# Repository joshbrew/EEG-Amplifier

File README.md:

## EEG Differential Amplifier

The main circuit here uses 4 low noise op amps to achieve EEG differential amplification. This should plug into any single ended ADC (or put your negative input to ground) to allow even as low as 10 bit EEG.

The amps cost 10 cents from TI, not including the PCB which will vary.

The reference design is for 1000x gain at 5v with a 2.5v voltage reference. All calculations are in the pdf for your needs.

### Resources
- [Differential Amp BOM](https://docs.google.com/spreadsheets/d/1rzFOKtwm5F1gYTblCt51H4664hxHK5iFGmpR6K0Omsg/edit?usp=sharing)
- [Gain Amp BOM](https://docs.google.com/spreadsheets/d/1fu1xdZPcOAWwaKk6sFUOHw02OROvW1wCZvjth2xU8xA/edit?usp=sharing)
- [Design reference](https://github.com/joshbrew/EEG-Amplifier/blob/main/EEG_Active_electrode_design.pdf) by Abishek Parikh. 
Other info pulled from datasheets.

Note my previous OPA202 config was incorrect. And use this formula for calculating the bandpass: 
<table>
  <tr>
    <td>
      <br/>
      In our config, + is our reference <br/> 
      (e.g. ear for EEG or opposite wrist for ECG)
    </td>
    <td>
      
    </td>
    <td>
      Gain = R2 / R1
    </td>
  </tr>
</table>

### OPA4202ID/TL084CDR/TL084OD (or compatible SOIC14) SMT mount.

OPA4202ID is more expensive but MUCH better quality, with better input impedance (3TΩ) and a 9nV/sqrt(Hz) noise density starting at 0.1Hz. The TL084's spectral noise doesn't bottom out until near 1kHz.

### 4mm Snap Button Electrode Mountholes

Sized for Florida Instruments reusable plastic snap electrodes.

### TL084HCN (A,B,H, etc) Thruhole amp (for DIY)

### OPA4202IPW or OPA4377 (or  compatible TSSOP14) SMT mount.

### Schematics

The BioAmp EXG Pill has a different layout you can check out. Same chipset.

### Noise vs Measured Bandwidth on OPA4202

Note: Noise calcs are probably inaccurate. Lower frequencies have higher noise density. Adjust bandpass accordingly.

TL084 noise density:

OPA4202 noise density:

OPA4202 or OPA4377 are about a dollar. I think the 4202 is better based on the noise.

## Also included in CAD/singular_amps

Single and Dual OPA202/OPA2202 gain amplifiers. E.g. for pre-amplification. Great low frequency noise density. 

### OPA202 (or pin compatible) VSSOP8 package (or pin compatible)

### OPA202 VSSOP8 package with 4mm electrode mount

### OPA202 SOIC8 package and thruhole resistors/capacitors (easier to hand solder)

### OPA202 SOIC8 package thruhole with 4mm electrode mount

EAGLE drawings by Josh Brewster. Works in free EAGLE or you can import them elsewhere usually.

Best prices are on TI.com just FYI...

Free source! Definitely question my circuitry before you use it.

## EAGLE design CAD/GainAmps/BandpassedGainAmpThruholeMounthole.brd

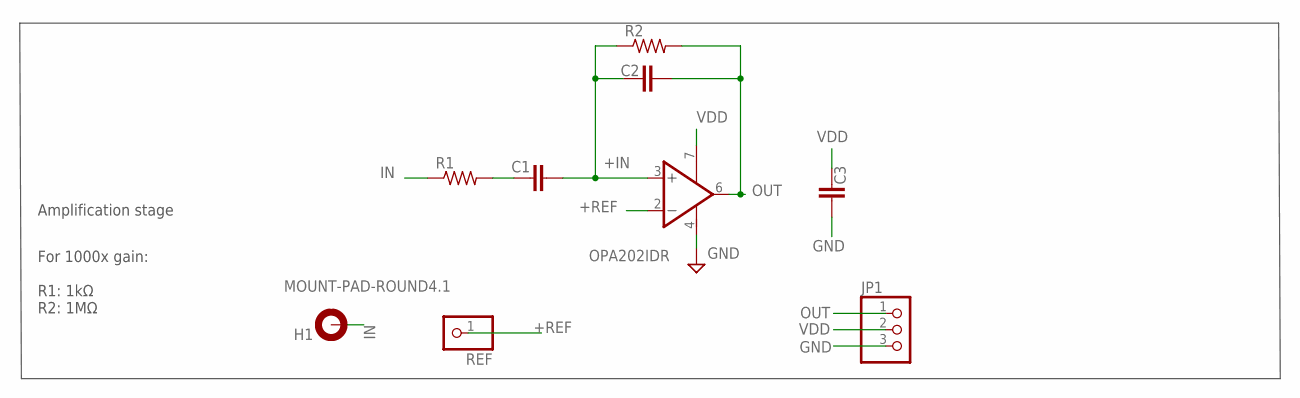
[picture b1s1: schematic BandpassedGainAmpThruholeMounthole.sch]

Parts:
C1, C2, C3: C2.5/2; C2.5-2
H1: MOUNT-PAD-ROUND4.1; 4,1-PAD
JP1: PINHD-1X3; 1X03
R1, R2: R-US_0204/5; 0204/5
REF: PINHD-1X1; 1X01
U1: OPA202IDR; SOIC127P600X175-8N

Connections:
+IN: C1.2, C2.1, R2.1, U1.3 (+IN)
+REF: REF.1, U1.2 (-IN)
GND: C3.2, JP1.3, U1.4 (V-)
IN: H1.B4,1, R1.1
OUT: C2.2, JP1.1, R2.2, U1.6 (OUT)
R1C1: C1.1, R1.2
VDD: C3.1, JP1.2, U1.7 (V+)

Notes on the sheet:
Amplification stage
For 1000x gain: R1: 1kΩ R2: 1MΩ

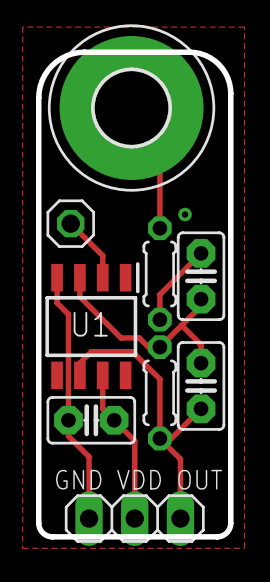
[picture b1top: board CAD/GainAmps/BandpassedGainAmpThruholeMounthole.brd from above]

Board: 2 copper layers, 10.7 x 26.9 mm, 9 parts (0 on the bottom side), 7 nets.

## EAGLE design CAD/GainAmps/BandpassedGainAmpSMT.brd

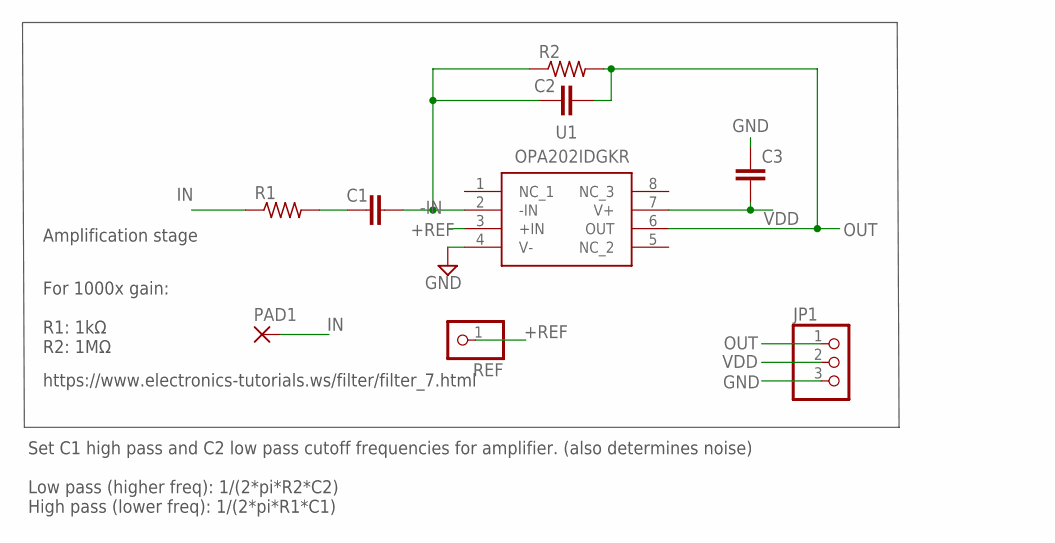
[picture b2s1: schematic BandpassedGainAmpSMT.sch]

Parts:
C1, C2, C3: C-EUC0402; C0402
JP1: PINHD-1X3; 1X03
PAD1: 3,17/1,1
R1, R2: R-US_R0402; R0402
REF: PINHD-1X1; 1X01
U1: OPA202IDGKR; SOP65P490X110-8N

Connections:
+REF: REF.1, U1.3 (+IN)
-IN: C1.2, C2.1, R2.1, U1.2 (-IN)
GND: C3.1, JP1.3, U1.4 (V-)
IN: PAD1.1, R1.1
OUT: C2.2, JP1.1, R2.2, U1.6 (OUT)
R1C1: C1.1, R1.2
VDD: C3.2, JP1.2, U1.7 (V+)

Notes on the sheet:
Amplification stage
For 1000x gain: R1: 1kΩ R2: 1MΩ
Set C1 high pass and C2 low pass cutoff frequencies for amplifier. (also determines noise) Low pass (higher freq): 1/(2*pi*R2*C2) High pass (lower freq): 1/(2*pi*R1*C1)
https://www.electronics-tutorials.ws/filter/filter_7.html

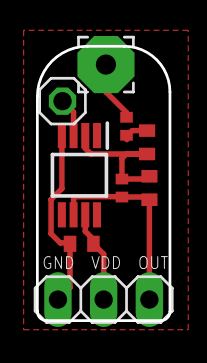
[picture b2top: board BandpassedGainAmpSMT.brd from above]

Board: 2 copper layers, 7.4 x 15.2 mm, 9 parts (0 on the bottom side), 7 nets.

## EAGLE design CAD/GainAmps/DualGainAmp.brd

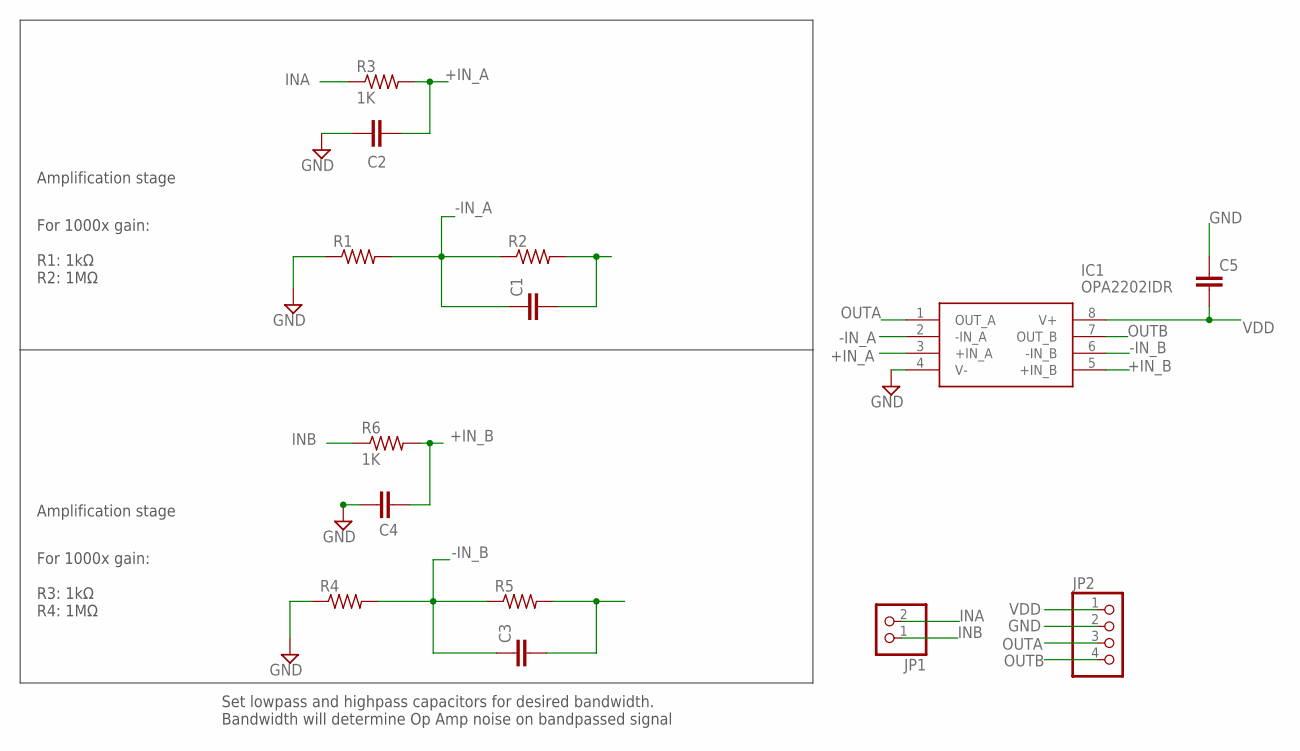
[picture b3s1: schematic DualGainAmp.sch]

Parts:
C1, C2, C3, C4: C-EUC0402; C0402
C5: C2.5/2; C2.5-2
IC1: OPA2202IDR; SOIC127P600X175-8N
JP1: PINHD-1X2; 1X02
JP2: PINHD-1X4; 1X04
R1, R2, R4, R5: R-US_0204/5; 0204/5
R3, R6: 1K; 0204/5

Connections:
+IN_A: C2.2, IC1.3 (+IN_A), R3.2
+IN_B: C4.2, IC1.5 (+IN_B), R6.2
-IN_A: C1.1, IC1.2 (-IN_A), R1.2, R2.1
-IN_B: C3.1, IC1.6 (-IN_B), R4.2, R5.1
GND: C2.1, C4.1, C5.1, IC1.4 (V-), JP2.2, R1.1, R4.1
INA: JP1.2, R3.1
INB: JP1.1, R6.1
unnamed: C1.2, R2.2
unnamed: C3.2, R5.2
OUTA: IC1.1 (OUT_A), JP2.3
OUTB: IC1.7 (OUT_B), JP2.4
VDD: C5.2, IC1.8 (V+), JP2.1

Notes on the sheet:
Amplification stage
For 1000x gain: R3: 1kΩ R4: 1MΩ
For 1000x gain: R1: 1kΩ R2: 1MΩ
Set lowpass and highpass capacitors for desired bandwidth. Bandwidth will determine Op Amp noise on bandpassed signal

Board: 2 copper layers, 14 parts (0 on the bottom side), 12 nets, no tracks yet.

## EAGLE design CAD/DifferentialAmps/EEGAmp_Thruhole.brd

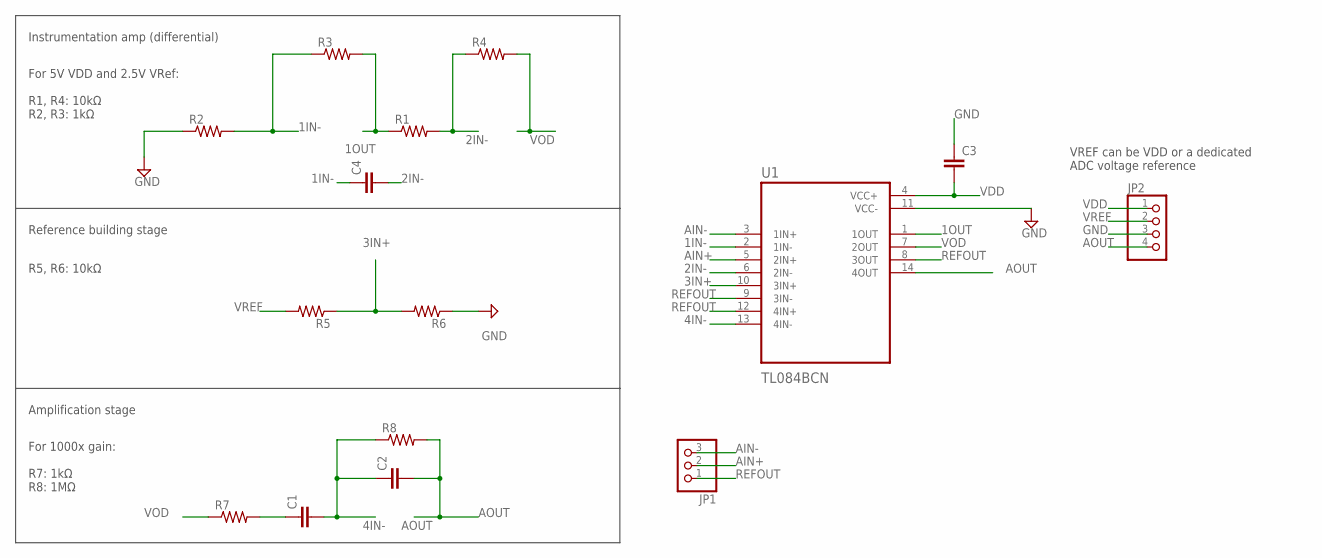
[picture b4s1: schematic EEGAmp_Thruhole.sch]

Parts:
C1, C2, C3, C4: C2.5/2; C2.5-2
JP1: PINHD-1X3; 1X03
JP2: PINHD-1X4; 1X04
R1, R2, R3, R4, R5, R6, R7, R8: R-US_0204/5; 0204/5
U1: TL084BCN; DIP794W45P254L1969H508Q14

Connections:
1IN-: C4.1, R2.2, R3.1, U1.2 (1IN-)
1OUT: R1.1, R3.2, U1.1 (1OUT)
2IN-: C4.2, R1.2, R4.1, U1.6 (2IN-)
3IN+: R5.1, R6.2, U1.10 (3IN+)
4IN-: C1.2, C2.1, R8.1, U1.13 (4IN-)
AIN+: JP1.2, U1.5 (2IN+)
AIN-: JP1.3, U1.3 (1IN+)
AOUT: C2.2, JP2.4, R8.2, U1.14 (4OUT)
GND: C3.1, JP2.3, R2.1, R6.1, U1.11 (VCC-)
unnamed: C1.1, R7.2
REFOUT: JP1.1, U1.8 (3OUT), U1.9 (3IN-), U1.12 (4IN+)
VDD: C3.2, JP2.1, U1.4 (VCC+)
VOD: R4.2, R7.1, U1.7 (2OUT)
VREF: JP2.2, R5.2

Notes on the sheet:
Instrumentation amp (differential)
Reference building stage
Amplification stage
For 5V VDD and 2.5V VRef: R1, R4: 10kΩ R2, R3: 1kΩ
R5, R6: 10kΩ
For 1000x gain: R7: 1kΩ R8: 1MΩ
VREF can be VDD or a dedicated ADC voltage reference

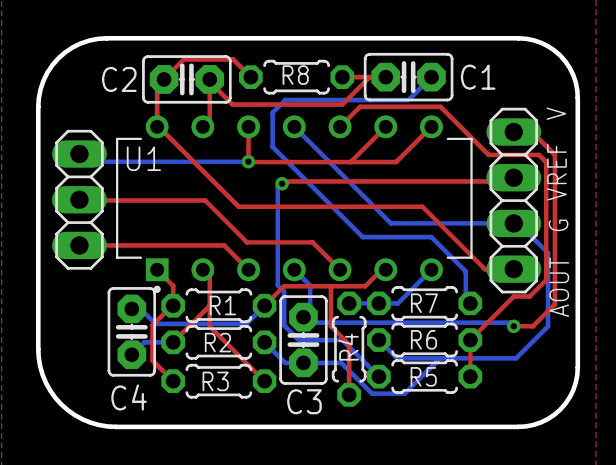
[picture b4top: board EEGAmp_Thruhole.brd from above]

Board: 2 copper layers, 30.0 x 21.6 mm, 15 parts (0 on the bottom side), 14 nets.

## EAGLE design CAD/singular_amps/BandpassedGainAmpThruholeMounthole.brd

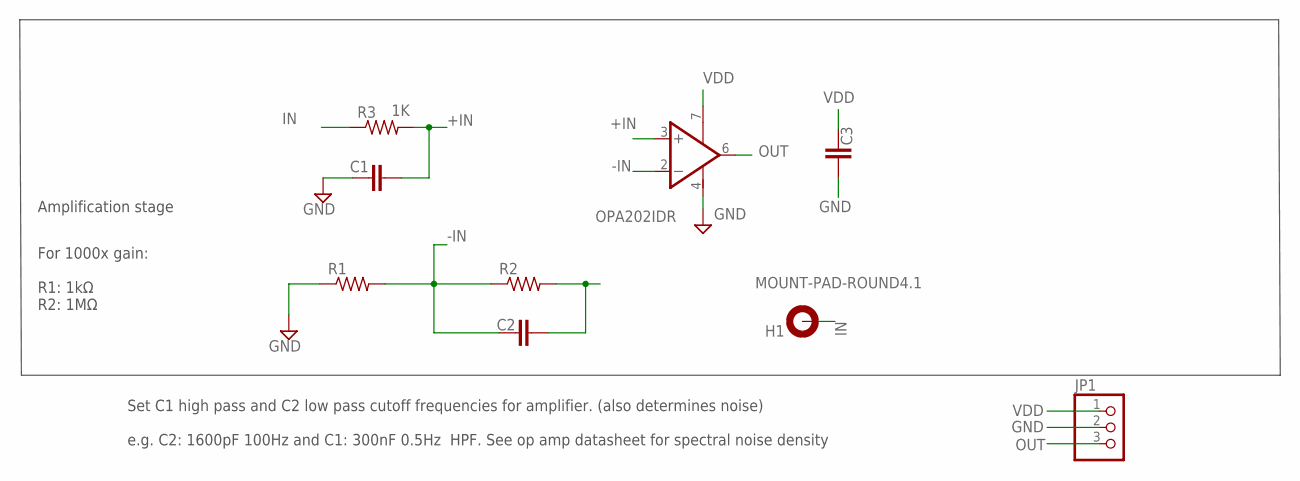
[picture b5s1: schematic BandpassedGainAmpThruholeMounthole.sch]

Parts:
C1, C2, C3: C2.5/2; C2.5-2
H1: MOUNT-PAD-ROUND4.1; 4,1-PAD
JP1: PINHD-1X3; 1X03
R1, R2: R-US_0204/5; 0204/5
R3: 1K; 0204/5
U1: OPA202IDR; SOIC127P600X175-8N

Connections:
+IN: C1.2, R3.2, U1.3 (+IN)
-IN: C2.1, R1.2, R2.1, U1.2 (-IN)
GND: C1.1, C3.2, JP1.2, R1.1, U1.4 (V-)
IN: H1.B4,1, R3.1
unnamed: C2.2, R2.2
OUT: JP1.3, U1.6 (OUT)
VDD: C3.1, JP1.1, U1.7 (V+)

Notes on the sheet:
Amplification stage
For 1000x gain: R1: 1kΩ R2: 1MΩ
Set C1 high pass and C2 low pass cutoff frequencies for amplifier. (also determines noise) e.g. C2: 1600pF 100Hz and C1: 300nF 0.5Hz HPF. See op amp datasheet for spectral noise density

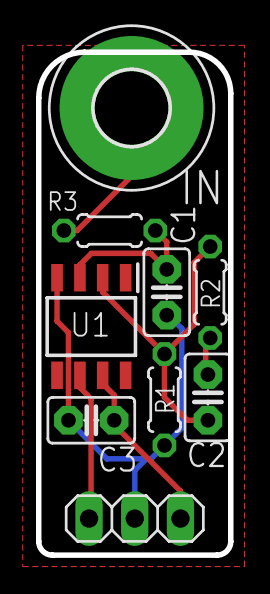
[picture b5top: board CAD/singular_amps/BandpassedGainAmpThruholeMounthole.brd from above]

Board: 2 copper layers, 10.7 x 27.9 mm, 9 parts (0 on the bottom side), 7 nets.

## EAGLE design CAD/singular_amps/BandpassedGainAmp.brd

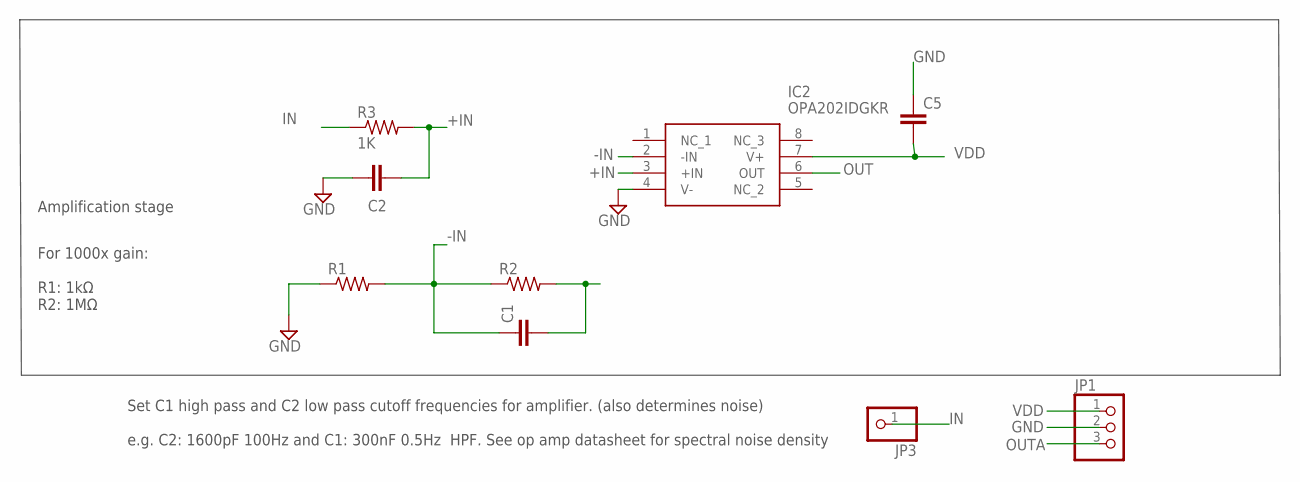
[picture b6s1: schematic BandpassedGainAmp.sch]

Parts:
C1, C2: C-EUC0402; C0402
C5: C2.5/2; C2.5-2
IC2: OPA202IDGKR; SOP65P490X110-8N
JP1: PINHD-1X3; 1X03
JP3: PINHD-1X1; 1X01
R1, R2: R-US_0204/5; 0204/5
R3: 1K; 0204/5

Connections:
+IN: C2.2, IC2.3 (+IN), R3.2
-IN: C1.1, IC2.2 (-IN), R1.2, R2.1
GND: C2.1, C5.1, IC2.4 (V-), JP1.2, R1.1
IN: JP3.1, R3.1
unnamed: C1.2, R2.2
OUT: IC2.6 (OUT)
OUTA: JP1.3
VDD: C5.2, IC2.7 (V+), JP1.1

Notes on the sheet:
Amplification stage
For 1000x gain: R1: 1kΩ R2: 1MΩ
Set C1 high pass and C2 low pass cutoff frequencies for amplifier. (also determines noise) e.g. C2: 1600pF 100Hz and C1: 300nF 0.5Hz HPF. See op amp datasheet for spectral noise density

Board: 2 copper layers, 9 parts (0 on the bottom side), 6 nets, no tracks yet.

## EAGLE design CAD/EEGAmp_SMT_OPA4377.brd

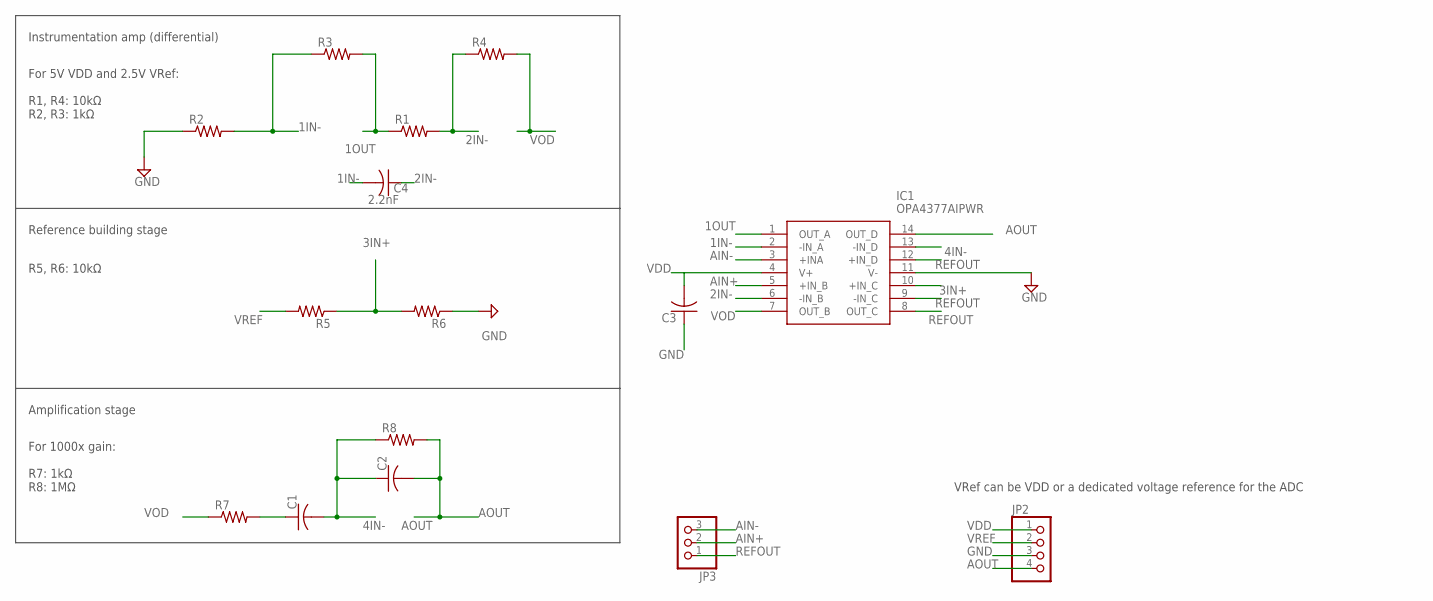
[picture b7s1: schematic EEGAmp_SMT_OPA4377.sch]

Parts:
C1, C2, C3: C-USC0402; C0402
C4: 2.2nF; C0402
IC1: OPA4377AIPWR; SOP65P640X120-14N
JP2: PINHD-1X4; 1X04
JP3: PINHD-1X3; 1X03
R1, R2, R3, R4, R5, R6, R7, R8: R-US_R0402; R0402

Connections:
1IN-: C4.2, IC1.2 (-IN_A), R2.2, R3.1
1OUT: IC1.1 (OUT_A), R1.1, R3.2
2IN-: C4.1, IC1.6 (-IN_B), R1.2, R4.1
3IN+: IC1.10 (+IN_C), R5.1, R6.2
4IN-: C1.2, C2.1, IC1.13 (-IN_D), R8.1
AIN+: IC1.5 (+IN_B), JP3.2
AIN-: IC1.3 (+INA), JP3.3
AOUT: C2.2, IC1.14 (OUT_D), JP2.4, R8.2
GND: C3.1, IC1.11 (V-), JP2.3, R2.1, R6.1
unnamed: C1.1, R7.2
REFOUT: IC1.8 (OUT_C), IC1.9 (-IN_C), IC1.12 (+IN_D), JP3.1
VDD: C3.2, IC1.4 (V+), JP2.1
VOD: IC1.7 (OUT_B), R4.2, R7.1
VREF: JP2.2, R5.2

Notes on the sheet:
Instrumentation amp (differential)
Reference building stage
Amplification stage
For 5V VDD and 2.5V VRef: R1, R4: 10kΩ R2, R3: 1kΩ
R5, R6: 10kΩ
For 1000x gain: R7: 1kΩ R8: 1MΩ
VRef can be VDD or a dedicated voltage reference for the ADC

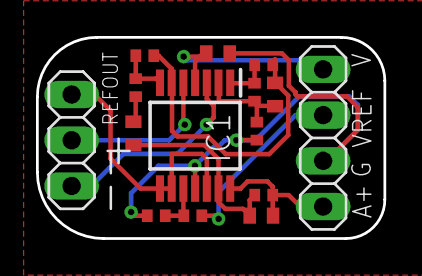
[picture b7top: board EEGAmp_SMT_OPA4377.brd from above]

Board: 2 copper layers, 19.3 x 11.2 mm, 15 parts (0 on the bottom side), 14 nets.

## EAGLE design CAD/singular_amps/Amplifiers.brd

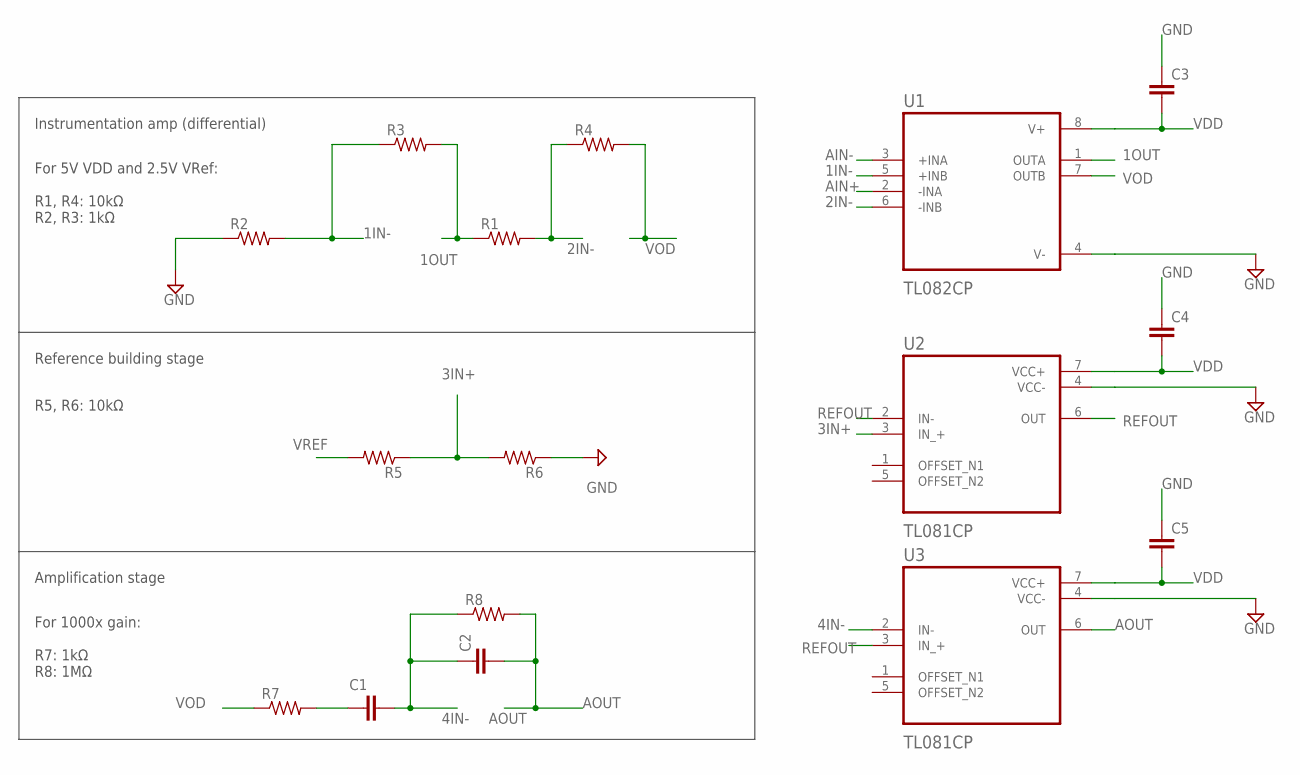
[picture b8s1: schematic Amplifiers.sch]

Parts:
C1, C2, C3, C4, C5: C2.5/2; C2.5-2
R1, R2, R3, R4, R5, R6, R7, R8: R-US_0204/5; 0204/5
U1: TL082CP; DIP794W45P254L959H508Q8
U2, U3: TL081CP; DIP794W45P254L959H508Q8

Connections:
1IN-: R2.2, R3.1, U1.5 (+INB)
1OUT: R1.1, R3.2, U1.1 (OUTA)
2IN-: R1.2, R4.1, U1.6 (-INB)
3IN+: R5.1, R6.2, U2.3 (IN_+)
4IN-: C1.2, C2.1, R8.1, U3.2 (IN-)
AIN+: U1.2 (-INA); also elsewhere on the board
AIN-: U1.3 (+INA); also elsewhere on the board
AOUT: C2.2, R8.2, U3.6 (OUT); also elsewhere on the board
GND: C3.1, C4.1, C5.1, R2.1, R6.1; also elsewhere on the board
unnamed: C1.1, R7.2
REFOUT: U2.2 (IN-), U2.6 (OUT), U3.3 (IN_+); also elsewhere on the board
VDD: C3.2, C4.2, C5.2; also elsewhere on the board
VOD: R4.2, R7.1, U1.7 (OUTB)
VREF: R5.2; also elsewhere on the board

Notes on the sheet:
Instrumentation amp (differential)
Reference building stage
Amplification stage
For 5V VDD and 2.5V VRef: R1, R4: 10kΩ R2, R3: 1kΩ
R5, R6: 10kΩ
For 1000x gain: R7: 1kΩ R8: 1MΩ

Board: 2 copper layers, 18 parts (0 on the bottom side), 14 nets, no tracks yet.

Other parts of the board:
JP2: 1X04
JP3: 1X03

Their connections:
AIN+: JP3.2; also elsewhere on the board
AIN-: JP3.3; also elsewhere on the board
AOUT: JP2.4; also elsewhere on the board
GND: JP2.3; also elsewhere on the board
REFOUT: JP3.1; also elsewhere on the board
VDD: JP2.1; also elsewhere on the board
VREF: JP2.2; also elsewhere on the board

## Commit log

2023-09-16 image
2023-09-16 add CAM
2023-09-16 smt version
2023-09-16 added mounthole version for integrating a snap electrode. More cam files,
2023-09-16 separate castellated mounthole and non castellated, more screenshots/links.
2023-09-16 add centroids
2023-09-16 update image
2023-09-16 fixed, smaller
2023-09-16 another wire tolerance fix
2023-09-16 and another wire fix
2023-09-17 fixed reference circuit (oops)
2023-09-17 add schematics png
2023-09-17 moved
2023-09-17 readded unfinished single amps w/ fix
2023-09-17 corrected notes
2023-09-18 added a filter cap on inputs
2023-09-18 screenshot
2023-09-18 add OPA4377 version (still can be made for ~1 dollar)
2023-09-18 added a couple non inverting gain amplifiers with bandpass filters
2023-09-28 finished gain amps
2023-09-28 moved, added production files for gain amps
2023-09-28 add BOM
2023-09-28 fixed edge plating
2023-09-28 fixed names
2024-07-26 fixing bandpass filters soon
2024-07-26 fixes
